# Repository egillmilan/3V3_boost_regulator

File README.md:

# 3V3 Boost Regulator
 A small 15x15mm boost regulator for powering 3.3V projects via one or two alkaline cells or other sources with voltages between 0.65V and 3.3V.

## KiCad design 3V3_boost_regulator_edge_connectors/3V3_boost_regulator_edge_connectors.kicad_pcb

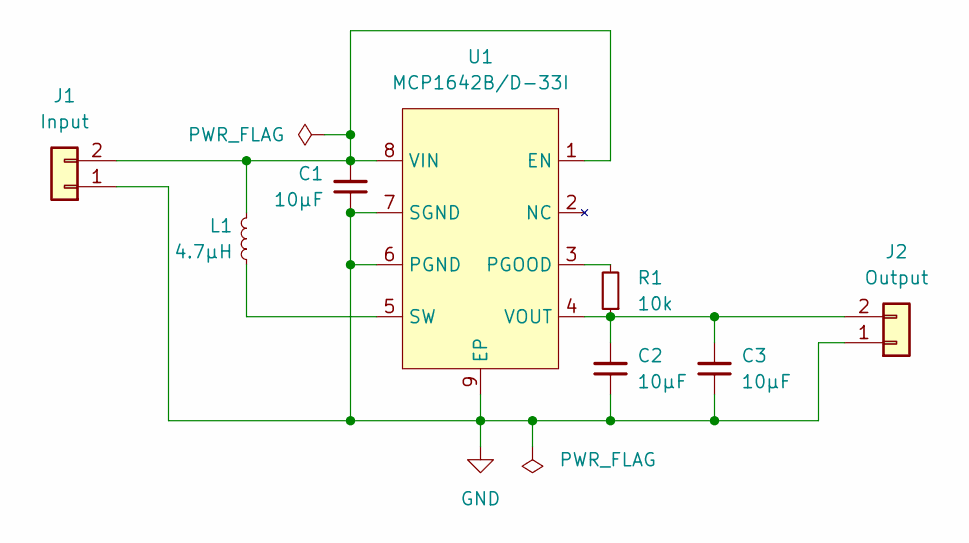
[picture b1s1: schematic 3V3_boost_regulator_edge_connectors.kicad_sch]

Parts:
C1, C2, C3: 10µF; C_0805_2012Metric_Pad1.18x1.45mm_HandSolder
J1: Input; PinHeader_1x02_P2.54mm_Vertical_with_Edge_Connector
J2: Output; PinHeader_1x02_P2.54mm_Vertical_with_Edge_Connector
L1: 4.7µH; B82462A4
R1: 10k; R_0805_2012Metric_Pad1.20x1.40mm_HandSolder
U1: MCP1642B/D-33I; DFN8_2x3mm_P0.5mm_EP1.45x1.75mm_hand_solder

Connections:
GND: C1.1, C2.1, C3.1, J1.1, J2.1, U1.6 (PGND), U1.7 (SGND), U1.9 (EP)
unnamed: C1.2, J1.2, L1.1, U1.1 (EN), U1.8 (VIN)
unnamed: C2.2, C3.2, J2.2, R1.1, U1.4 (VOUT)
unnamed: L1.2, U1.5 (SW)
unnamed: R1.2, U1.3 (PGOOD)

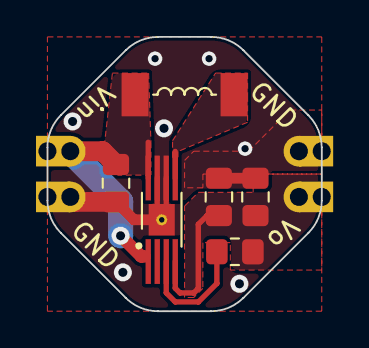
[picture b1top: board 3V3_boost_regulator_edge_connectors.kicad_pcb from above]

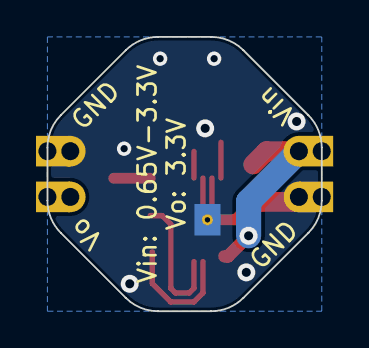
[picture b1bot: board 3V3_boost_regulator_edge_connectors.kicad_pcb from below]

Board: 2 copper layers, 15.2 x 15.2 mm, 8 parts (2 on the bottom side), 5 nets.

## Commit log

2022-04-03 Footprint updates
2022-04-03 Footprint fixes
2022-04-04 Updated 3D models
2022-04-11 Adjusted inductor pours
2022-04-16 Added castellations and fixed mistakes
2022-04-16 Cleanup
2022-04-16 Fixed 3D models
2022-04-28 Minor changes
2022-05-20 minor fix
